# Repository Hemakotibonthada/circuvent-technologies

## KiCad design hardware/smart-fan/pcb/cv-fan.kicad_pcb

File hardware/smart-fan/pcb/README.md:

# Smart Fan PCB - KiCad project + fab checklist

Design source: SCHEMATIC.md (netlist) + BOM.csv. Open cv-fan.kicad_pro in KiCad 8, capture, lay out, export.

## Board spec
- 2-layer FR4, 1.6 mm, HASL lead-free, 2 oz copper on mains.
- >= 8 mm creepage / 6 mm clearance mains-to-LV; isolation slots.
- Size target ~ 55 x 45 mm; 2x M3.
- Op-amp + RC near IO25; guard the 0-10 V trace from PWM/mains coupling.

## Pre-fab (DFM) checklist
- [ ] ERC/DRC clean at fab rules; mains clearances as keepout
- [ ] Fuse + MOV at entry; relay pad wide
- [ ] RC + op-amp gain verified for full 0-10 V swing
- [ ] Test points: 5V, 3V3, GND, IO26/25, 0-10 V out
- [ ] UART/EN/IO0 pads for the flashing jig; fiducials

## Export for fab / assembly
- [ ] Gerbers + Excellon -> gerbers/; IPC-356 netlist
- [ ] BOM (BOM.csv) + CPL/centroid; PDF assembly + 3D STEP
- [ ] Order boards + stencil

## Bring-up (EVT)
- [ ] Rails before ESP32; flash test firmware over jig
- [ ] Relay clicks + powers the fan; 0-10 V ramps 0-100%
- [ ] Button cycles presets offline
- [ ] Cloud sync self-test; schedule fires

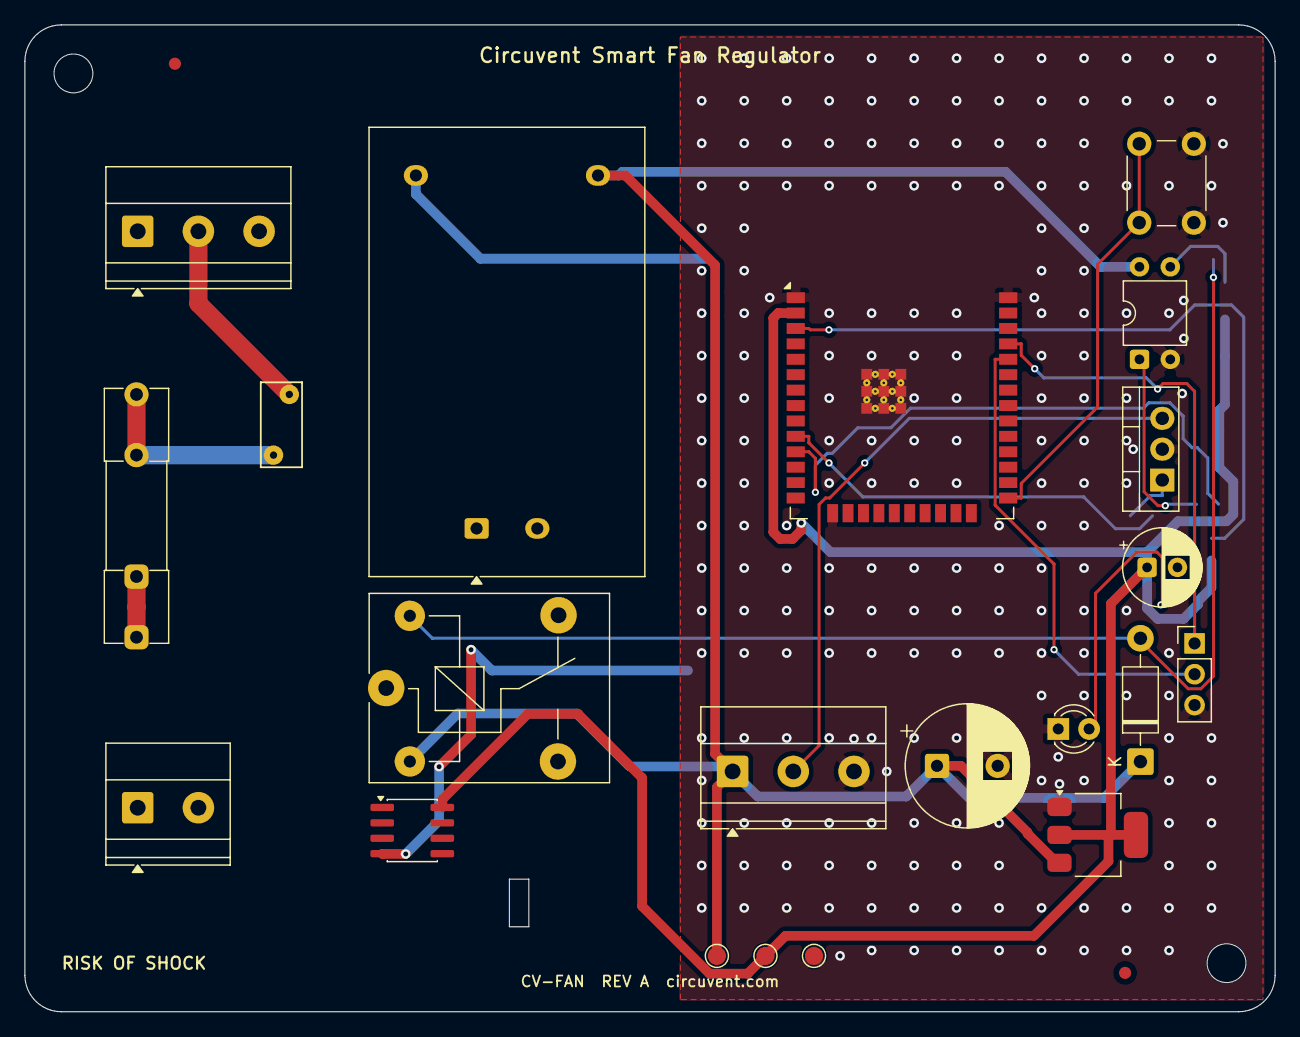
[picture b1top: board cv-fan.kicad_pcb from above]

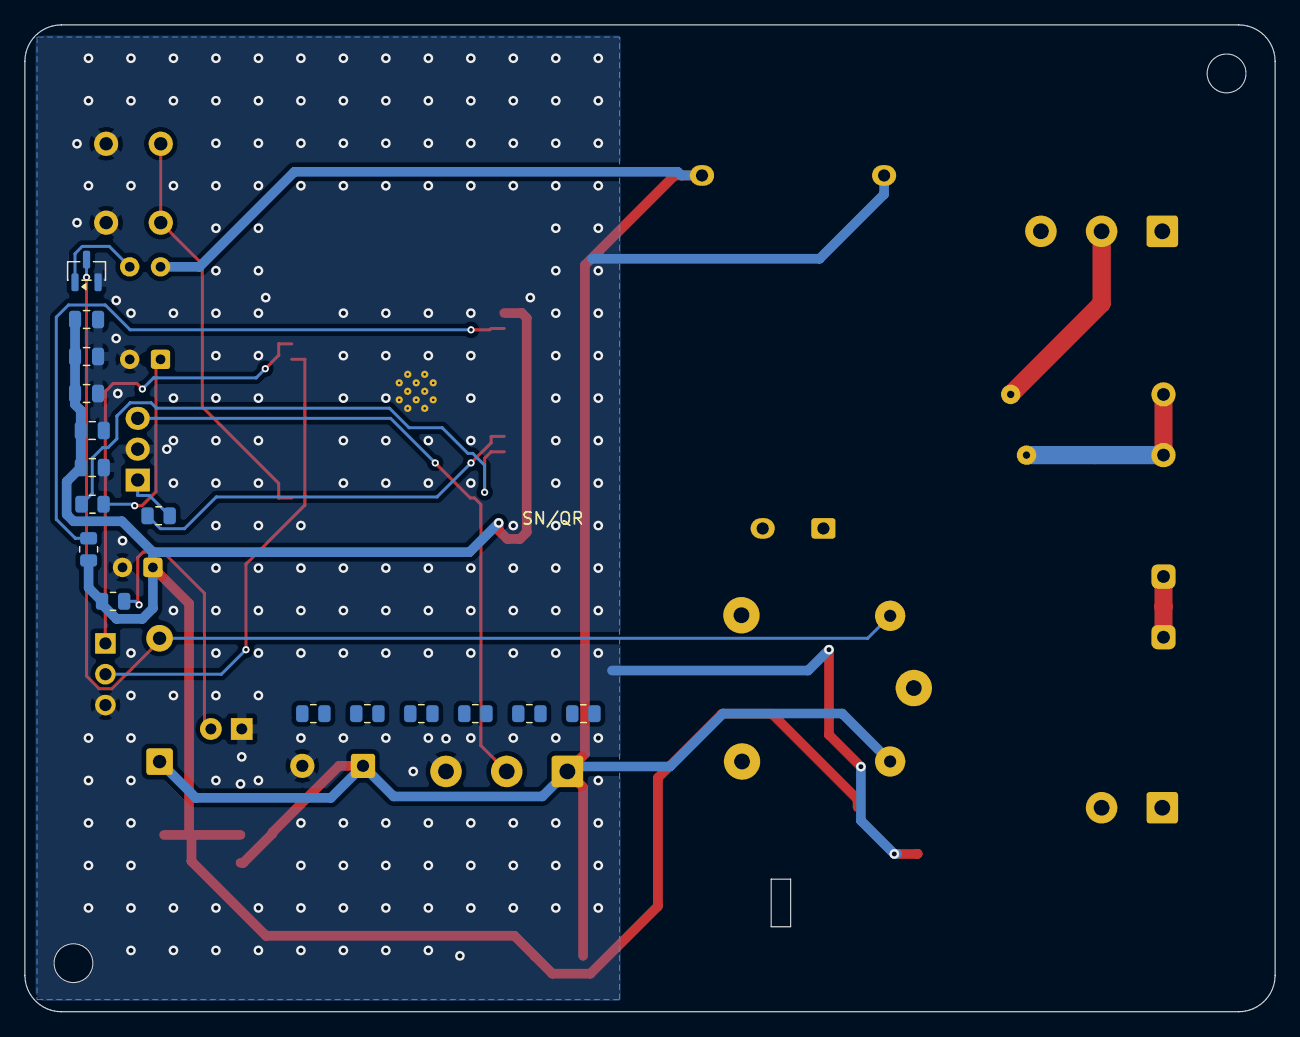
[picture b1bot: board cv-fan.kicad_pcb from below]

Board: 2 copper layers, 103.0 x 81.3 mm, 41 parts (16 on the bottom side), 19 nets.

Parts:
C1: 470uF/10V; CP_Radial_D10.0mm_P5.00mm
C2: 100uF/6.3V; CP_Radial_D6.3mm_P2.50mm
C3, C4, C5, C6: 100nF; C_0805_2012Metric
Cf: 1uF film; C_0805_2012Metric
D1: 1N4007; D_DO-41_SOD81_P10.16mm_Horizontal
F1: 2A slow-blow; Fuseholder_Clip-5x20mm_Littelfuse_111_Inline_P20.00x5.00mm_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
FID1, FID2: Fiducial; Fiducial_1mm_Mask2mm
J1: 2P 5.08mm; TerminalBlock_Phoenix_MKDS-1,5-3_1x03_P5.00mm_Horizontal
J2: 2P 5.08mm; TerminalBlock_Phoenix_MKDS-1,5-2_1x02_P5.00mm_Horizontal
J3: 3P 5.08mm; TerminalBlock_Phoenix_MKDS-1,5-3_1x03_P5.00mm_Horizontal
JP: 3P 2.54mm; PinHeader_1x03_P2.54mm_Vertical
K1: SRD-05VDC-SL-C; Relay_SPDT_SANYOU_SRD_Series_Form_C
LED0: Green 3mm; LED_D3.0mm
MH1, MH2: MountingHole; MountingHole_3.2mm_M3
PC1: PC817; DIP-4_W7.62mm
PS1: HLK-PM03 (5V 3W); Converter_ACDC_Hi-Link_HLK-PMxx
Q1: S8050; SOT-23
Qm: IRLZ44N; TO-220-3_Vertical
R1, R2, R3, R4, R5, R6, R7, R8, R9, R10: 10k/1k/330 + RC; R_0805_2012Metric
RV1: 7D471K; RV_Disc_D7mm_W3.4mm_P5mm
SW1: Tactile 6mm; SW_PUSH_6mm_H5mm
TP1: +5V; TestPoint_Pad_D1.5mm
TP2: +3V3; TestPoint_Pad_D1.5mm
TP3: GND; TestPoint_Pad_D1.5mm
U1: ESP32-WROOM-32E (4MB); ESP32-WROOM-32E
U2: AMS1117-3.3; SOT-223-3_TabPin2
U3: MCP6002; SOIC-8_3.9x4.9mm_P1.27mm

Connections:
+3V3: C2.1, C3.1, C4.1, C5.1, C6.1, Cf.1, R3.1, R4.1, TP2.1, U1.2, U2.2, U3.8
+5V: C1.1, D1.1, J3.1, K1.2, PC1.4, PS1.4, TP1.1, U2.3
AC_L: F1.1, J1.1
AC_L_FUSED: F1.2, K1.1, PS1.1, RV1.1, U3.1
AC_N: J1.2, J2.2, PS1.2, RV1.2
BTN_PIN: SW1.1, U1.25
EN: R3.2, U1.3
FAN_RELAY: R1.1, U1.11
FAN_RELAY_COIL: D1.2, K1.5, Q1.3
FAN_RELAY_DRV: PC1.3, Q1.1
FAN_RELAY_OPT: PC1.1, R1.2
FAN_RELAY_SW: J2.1, K1.3
GND: C1.2, C2.2, C3.2, C4.2, C5.2, C6.2, Cf.2, J3.3, JP.3, LED0.1, PC1.2, PS1.3, Q1.2, Qm.2, SW1.2, TP3.1, U1.1, U1.15, U1.38, U1.39, U2.1, U3.4
LED0_A: LED0.2, R4.2
SPEED_PWM_PIN: R2.1, U1.10
SPEED_PWM_PIN_B: Qm.1, R2.2
SPEED_PWM_PIN_OUT: J3.2, Qm.3
UART_RX: JP.2, U1.34
UART_TX: JP.1, U1.35

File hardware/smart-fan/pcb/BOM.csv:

Ref,Qty,Value/Part,Package,Description,Notes
U1,1,ESP32-WROOM-32E (4MB),SMD module,Wi-Fi/BLE MCU module,Main controller
PS1,1,HLK-PM03 (5V 3W),SIP,230VAC -> 5VDC isolated PSU,Relay + logic
U2,1,AMS1117-3.3,SOT-223,5V -> 3.3V LDO,MCU rail
U3,1,MCP6002,SOIC-8,Rail-to-rail op-amp,0-10 V speed buffer
PC1,1,PC817,DIP-4,Opto-isolator,Relay drive
Q1,1,S8050,SOT-23,NPN relay driver,
Qm,1,IRLZ44N,TO-220,N-MOSFET (DC-fan option),Optional
D1,1,1N4007,DO-41,Flyback diode,Relay coil
K1,1,SRD-05VDC-SL-C,THT relay,5V SPDT,Fan power
RV1,1,7D471K,disc,MOV 470V,Mains surge clamp
F1,1,2A slow-blow,5x20 holder,Mains fuse,
SW1,1,Tactile 6mm,THT,Button / BOOT,
LED0,1,Green 3mm,THT,Power/online,
J1,1,2P 5.08mm,terminal,Mains L/N in,
J2,1,2P 5.08mm,terminal,Fan power out,
J3,1,3P 5.08mm,terminal,0-10 V + GND (+ DC fan),
JP,1,3P 2.54mm,header,UART (TX/RX/GND),Factory flashing
R1-R10,10,10k/1k/330 + RC,0805,Pull/base/LED/filter,
C1,1,470uF/10V,electrolytic,5V bulk,
C2,1,100uF/6.3V,electrolytic,3.3V rail,
Cf,1,1uF film,0805,RC filter cap,0-10 V smoothing
C3-C6,4,100nF,0805,Decoupling,
PCB,1,2-layer FR4 1.6mm,-,Main board,>=8mm mains-LV creepage; 2oz Cu
ENC,1,ABS wall box (UL94 V-0),-,Regulator box,Button + LED + brand area

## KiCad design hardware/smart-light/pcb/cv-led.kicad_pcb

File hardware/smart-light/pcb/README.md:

# Smart Light PCB - KiCad project + fab checklist

Design source: SCHEMATIC.md (netlist) + BOM.csv. Open cv-led.kicad_pro in KiCad 8, capture, lay out, export.

## Board spec
- 2-layer FR4, 1.6 mm, HASL lead-free, 1-2 oz copper on channels.
- Low-voltage DC only - no mains isolation required.
- Size target ~ 55 x 40 mm; 2x M3.
- Copper pour + optional heatsink on the MOSFET drains for high-current strips.

## Pre-fab (DFM) checklist
- [ ] ERC/DRC clean at fab rules
- [ ] Reverse-polarity diode + fuse on Vin
- [ ] MOSFET + trace width sized for per-channel current
- [ ] Test points: Vin, 5V, 3V3, GND, IO25/32/33/27/26
- [ ] UART/EN/IO0 pads for the flashing jig; fiducials

## Export for fab / assembly
- [ ] Gerbers + Excellon -> gerbers/; IPC-356 netlist
- [ ] BOM (BOM.csv) + CPL/centroid; PDF assembly + 3D STEP
- [ ] Order boards + stencil

## Bring-up (EVT)
- [ ] Rails before ESP32; flash test firmware over jig
- [ ] Each colour + white fades smoothly; aux relay clicks
- [ ] Button cycles presets offline
- [ ] Cloud sync self-test; scene fires

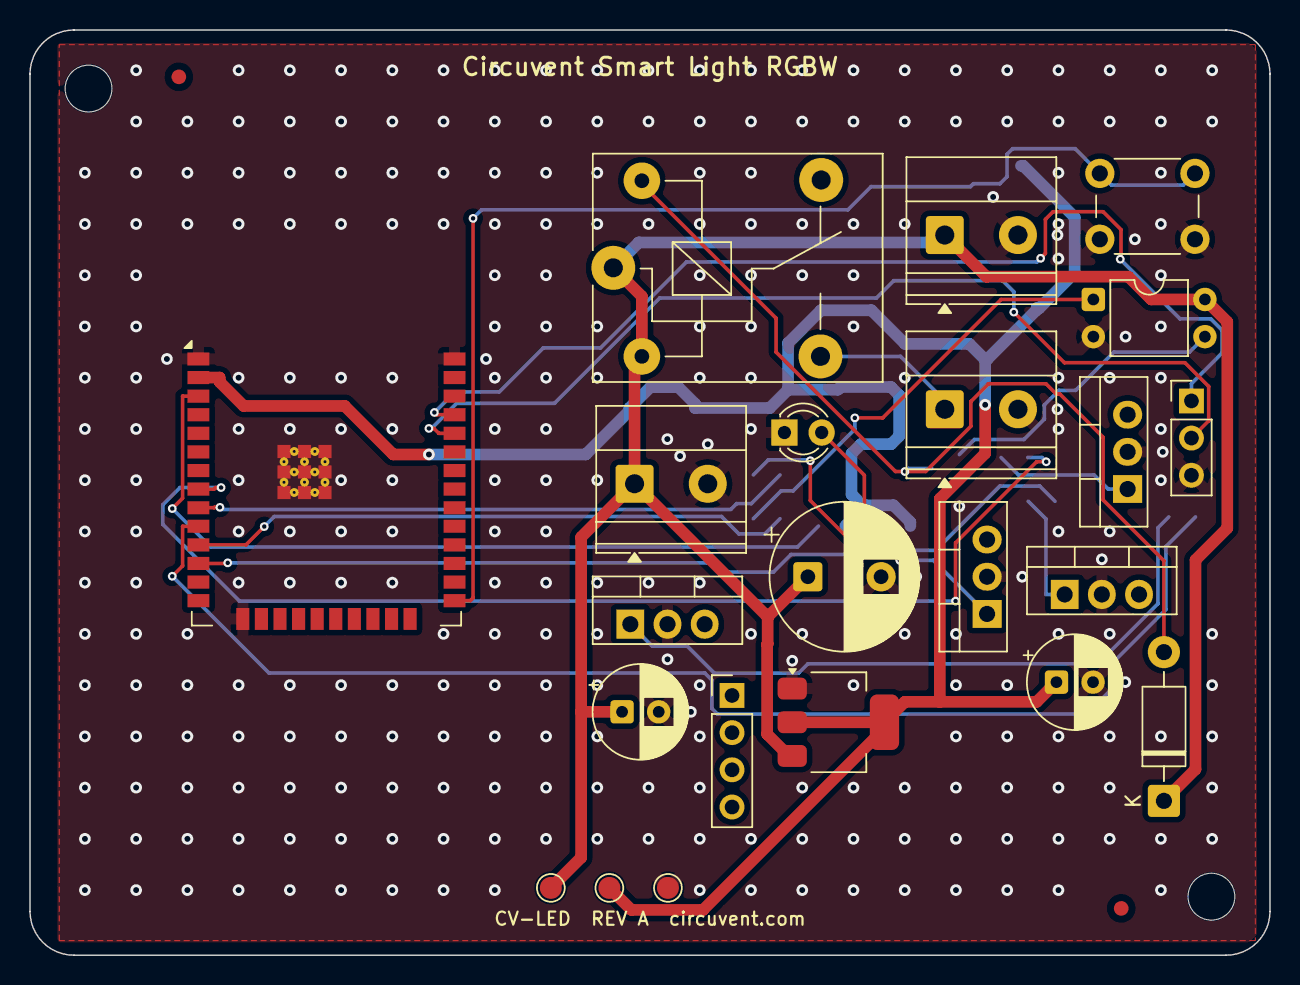
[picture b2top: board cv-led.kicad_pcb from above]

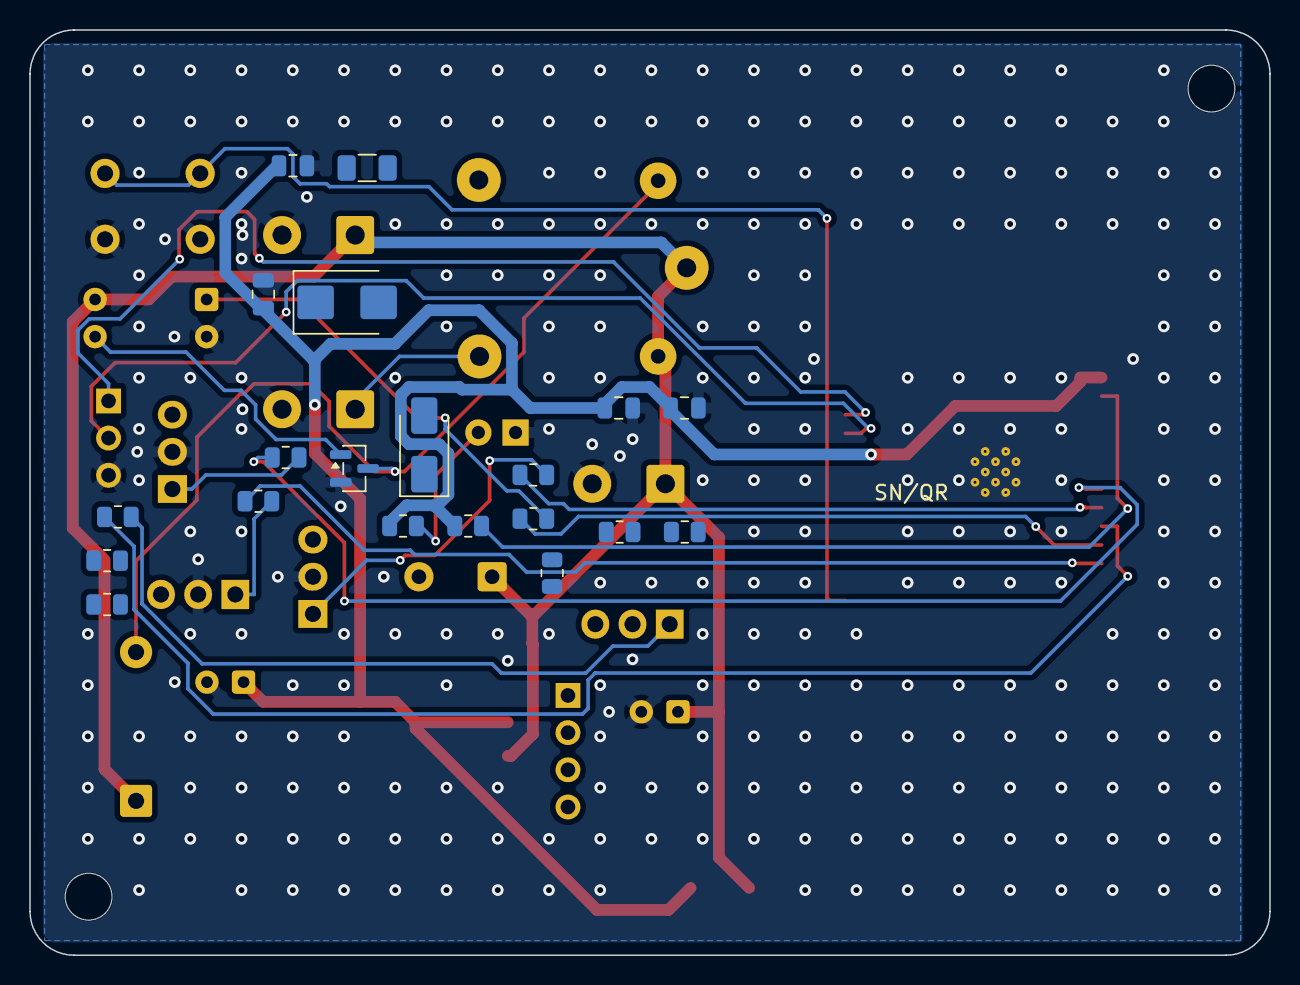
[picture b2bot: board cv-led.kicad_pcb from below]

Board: 2 copper layers, 84.7 x 63.2 mm, 46 parts (20 on the bottom side), 21 nets.

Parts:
C1: 470uF/35V; CP_Radial_D10.0mm_P5.00mm
C2, C3: 100uF; CP_Radial_D6.3mm_P2.50mm
C4, C5, C6, C7: 100nF; C_0805_2012Metric
D1: 1N4007; D_DO-41_SOD81_P10.16mm_Horizontal
D2: SS34; D_SMA
F1: 5A; Fuse_1206_3216Metric
FID1, FID2: Fiducial; Fiducial_1mm_Mask2mm
J1: 2P 5.08mm + barrel; TerminalBlock_Phoenix_MKDS-1,5-2_1x02_P5.00mm_Horizontal
J2: 5P 5.08mm; TerminalBlock_Phoenix_MKDS-1,5-2_1x02_P5.00mm_Horizontal
J3: 2P 5.08mm; TerminalBlock_Phoenix_MKDS-1,5-2_1x02_P5.00mm_Horizontal
JP: 3P 2.54mm; PinHeader_1x03_P2.54mm_Vertical
K1: SRD-05VDC-SL-C; Relay_SPDT_SANYOU_SRD_Series_Form_C
LED0: Green 3mm; LED_D3.0mm
MH1, MH2: MountingHole; MountingHole_3.2mm_M3
PC1: PC817; DIP-4_W7.62mm
Q1, Q2, Q3, Q4: AO3400 / IRLZ44N; TO-220-3_Vertical
Q5: S8050; SOT-23
R1, R2, R3, R4, R5, R6, R7, R8, R9, R10, R11, R12: 100R/100k/10k/330; R_0805_2012Metric
SW1: Tactile 6mm; SW_PUSH_6mm_H5mm
TP1: +5V; TestPoint_Pad_D1.5mm
TP2: +3V3; TestPoint_Pad_D1.5mm
TP3: GND; TestPoint_Pad_D1.5mm
TVS1: SMBJ33A; D_SMB
U1: ESP32-WROOM-32E (4MB); ESP32-WROOM-32E
U2: AMS1117-3.3; SOT-223-3_TabPin2
U3: MP1584 buck; PinHeader_1x04_P2.54mm_Vertical

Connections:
+3V3: C2.1, C4.1, C5.1, C6.1, C7.1, R6.1, R7.1, TP2.1, U1.2, U2.2
+5V: C1.1, C3.1, D1.1, J1.1, J3.1, K1.1, K1.2, PC1.4, TP1.1, U2.3
BTN_PIN: SW1.1, U1.25
EN: R6.2, U1.3
GND: C1.2, C2.2, C3.2, C4.2, C5.2, C6.2, C7.2, J1.2, J2.2, J3.2, JP.3, LED0.1, PC1.2, Q1.2, Q2.2, Q3.2, Q4.2, Q5.2, SW1.2, TP3.1, U1.1, U1.15, U1.38, U1.39, U2.1
LED0_A: LED0.2, R7.2
RELAY_PIN: R5.1, U1.11
RELAY_PIN_COIL: D1.2, K1.5, Q5.3
RELAY_PIN_DRV: PC1.3, Q5.1
RELAY_PIN_OPT: PC1.1, R5.2
RELAY_PIN_SW: J2.1, K1.3
RGB_B_PIN: R3.1, U1.12
RGB_B_PIN_B: Q3.1, R3.2
RGB_G_PIN: R2.1, U1.9
RGB_G_PIN_B: Q2.1, R2.2
RGB_R_PIN: R1.1, U1.8
RGB_R_PIN_B: Q1.1, R1.2
UART_RX: JP.2, U1.34
UART_TX: JP.1, U1.35
WHITE_PWM_PIN: R4.1, U1.10
WHITE_PWM_PIN_B: Q4.1, R4.2

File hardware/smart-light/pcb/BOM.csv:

Ref,Qty,Value/Part,Package,Description,Notes
U1,1,ESP32-WROOM-32E (4MB),SMD module,Wi-Fi/BLE MCU module,Main controller
U3,1,MP1584 buck,module/SMD,12-24V -> 5V DC-DC,Strip PSU rail
U2,1,AMS1117-3.3,SOT-223,5V -> 3.3V LDO,MCU rail
Q1-Q4,4,AO3400 / IRLZ44N,SOT-23 / TO-220,N-MOSFET PWM channels,R/G/B/W
Q5,1,S8050,SOT-23,NPN relay driver,Aux
PC1,1,PC817,DIP-4,Opto-isolator,Aux relay
K1,1,SRD-05VDC-SL-C,THT relay,5V SPDT,Aux fixture
D1,1,1N4007,DO-41,Flyback diode,Aux coil
D2,1,SS34,SMA,Reverse-polarity diode,Vin
TVS1,1,SMBJ33A,SMB,Transient suppressor,Vin surge
F1,1,5A,1206 fuse,Input fuse,
SW1,1,Tactile 6mm,THT,Button / BOOT,
LED0,1,Green 3mm,THT,Power/online,
J1,1,2P 5.08mm + barrel,terminal,Vin +/-,
J2,1,5P 5.08mm,terminal,+V R G B W,Strip out
J3,1,2P 5.08mm,terminal,Aux dry contact,
JP,1,3P 2.54mm,header,UART (TX/RX/GND),Factory flashing
R1-R12,12,100R/100k/10k/330,0805,Gate/pull/LED resistors,
C1,1,470uF/35V,electrolytic,Vin bulk,
C2-C3,2,100uF,electrolytic,5V + 3.3V,
C4-C7,4,100nF,0805,Decoupling,
PCB,1,2-layer FR4 1.6mm,-,Main board,MOSFET thermal pour
ENC,1,ABS inline box (UL94 V-0),-,Strip controller box,DC + terminal outs
